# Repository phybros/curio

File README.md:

# CURIO

CURIO is an ESP8266 based dev board!

This repo is the KiCAD project for the board.

## Features

* USB-C
* ESP-12E/F WiFi module
* Compatible with Arduino
* Breadboard friendly
* Voltage divider for the `ADC0` pin

## More info

A more detailed writeup on the development of this board can be found at 
<https://willwarren.com/2023/05/09/curio-an-esp-12f-based-dev-board/>!

## License

This repo is licensed under Creative Commons Attribution-ShareAlike 4.0 
International.

Read the full license here: [LICENSE.txt](LICENSE.txt)

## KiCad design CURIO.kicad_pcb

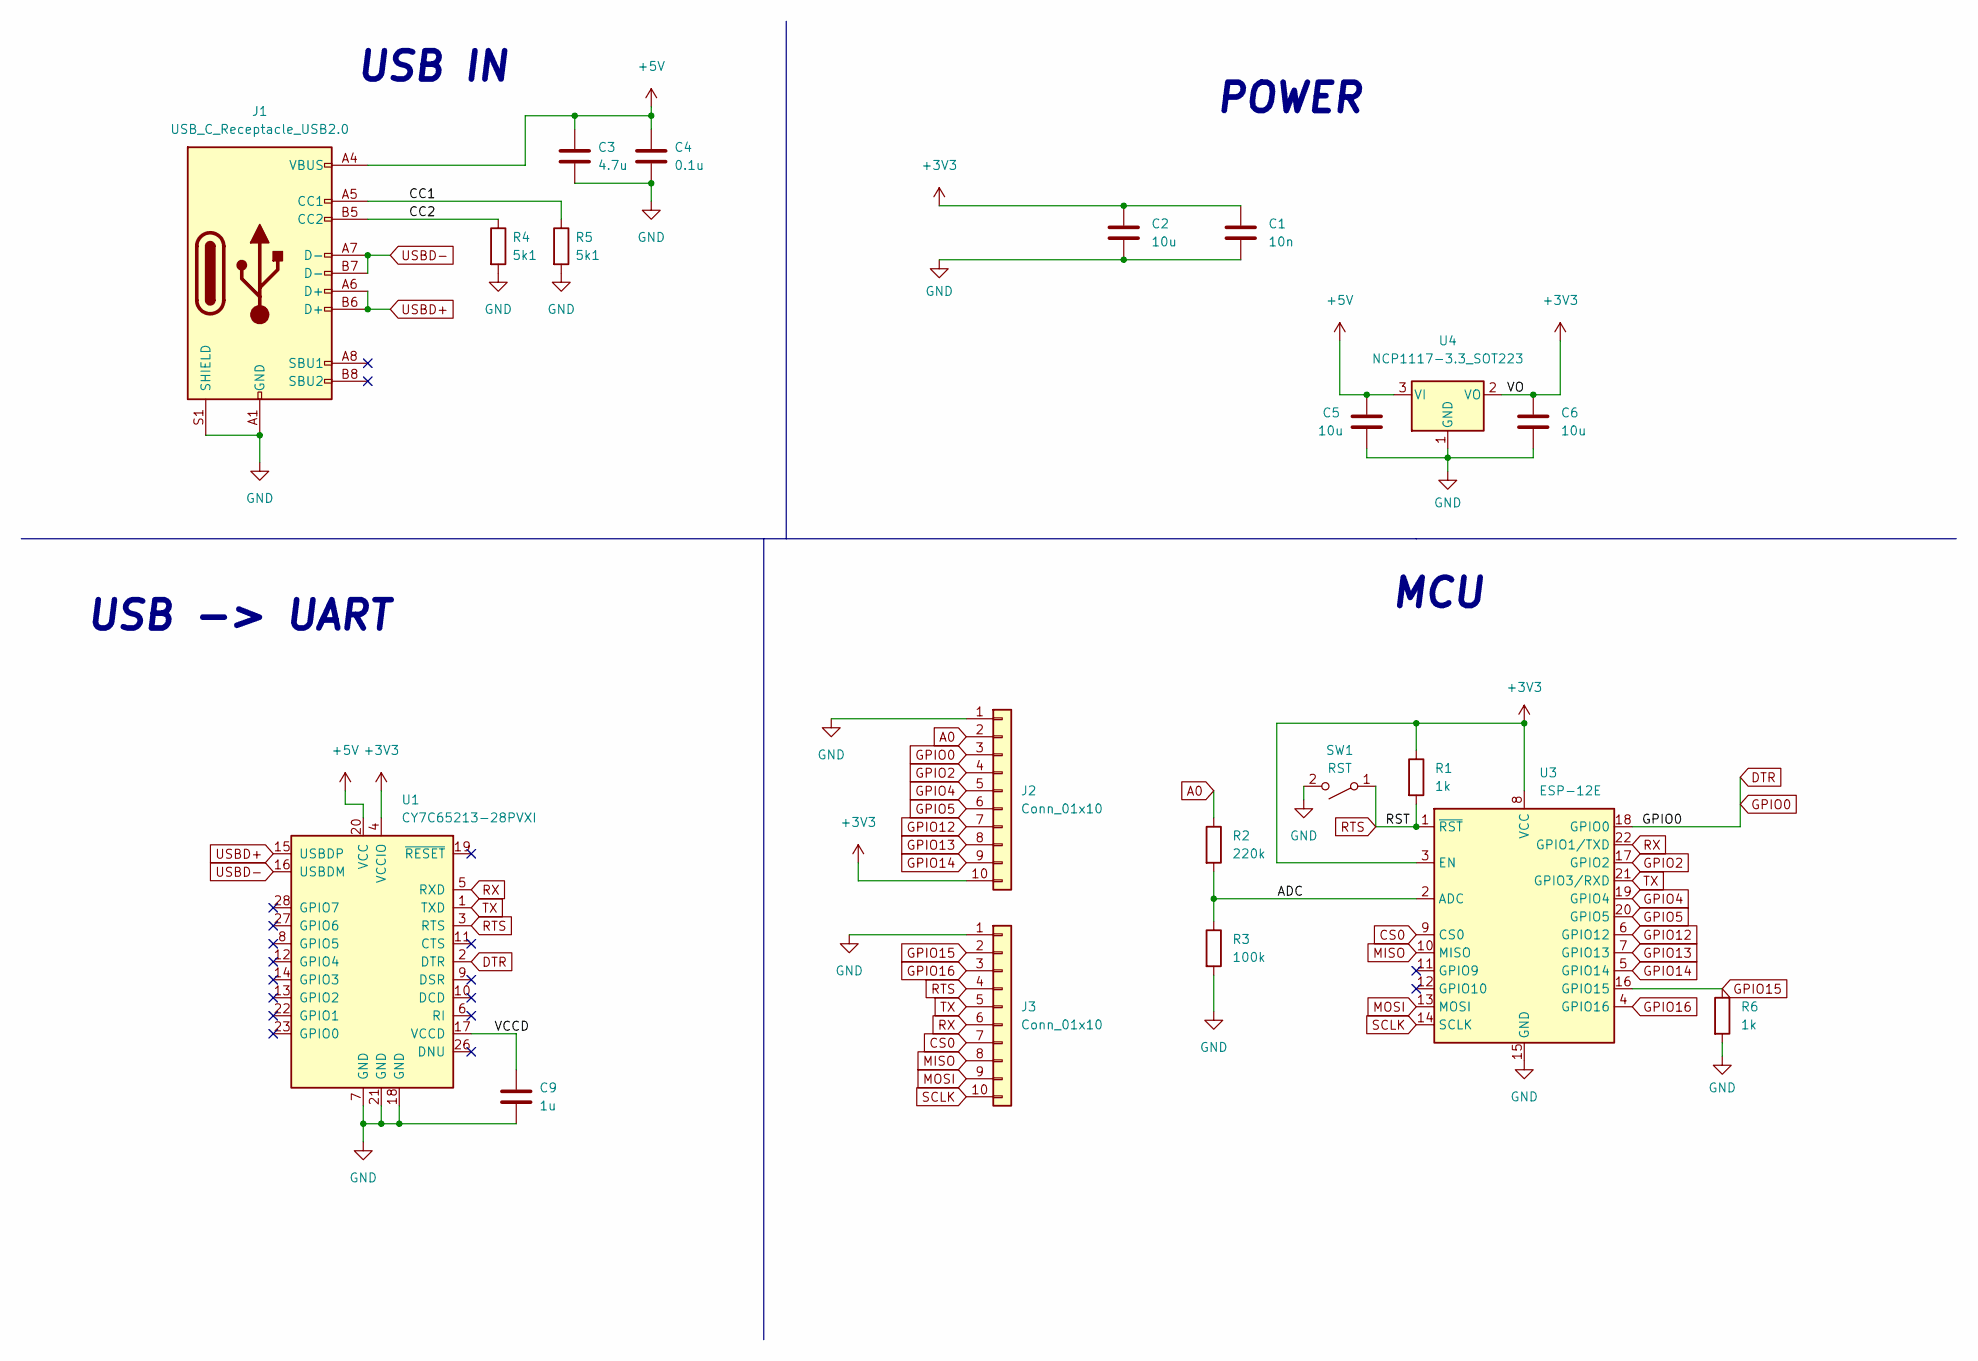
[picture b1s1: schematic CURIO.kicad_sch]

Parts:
C1: 10n; C_0402_1005Metric
C2, C5, C6: 10u; C_0402_1005Metric
C3: 4.7u; C_0402_1005Metric
C4: 0.1u; C_0402_1005Metric
C9: 1u; C_0402_1005Metric
J1: USB_C_Receptacle_USB2.0; USB_C_Receptacle_JAE_DX07S016JA1R1500
J2, J3: Conn_01x10; PinHeader_1x10_P2.54mm_Vertical
R1, R6: 1k; R_0402_1005Metric
R2: 220k; R_0402_1005Metric
R3: 100k; R_0402_1005Metric
R4, R5: 5k1; R_0402_1005Metric
SW1: RST; SW_SPST_B3U-1100P
U1: CY7C65213-28PVXI; SSOP-28_5.3x10.2mm_P0.65mm
U3: ESP-12E
U4: NCP1117-3.3_SOT223; SOT-223-3_TabPin2

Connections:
+3V3: C1.1, C2.1, C6.1, J2.10, R1.1, U1.4 (VCCIO), U3.3 (EN), U3.8 (VCC), U4.2 (VO)
+5V: C3.1, C4.1, C5.1, J1.A4 (VBUS), J1.A9 (VBUS), J1.B4 (VBUS), J1.B9 (VBUS), U1.20 (VCC), U4.3 (VI)
/ADC: R2.2, R3.1, U3.2 (ADC)
/CC1: J1.A5 (CC1), R5.1
/CC2: J1.B5 (CC2), R4.1
/VCCD: C9.1, U1.17 (VCCD)
A0: J2.2, R2.1
CS0: J3.7, U3.9 (CS0)
DTR: J2.3, U1.2 (DTR), U3.18 (GPIO0)
GND: C1.2, C2.2, C3.2, C4.2, C5.2, C6.2, C9.2, J1.A1 (GND), J1.A12 (GND), J1.B1 (GND), J1.B12 (GND), J1.S1 (SHIELD), J2.1, J3.1, R3.2, R4.2, R5.2, R6.2, SW1.2 (B), U1.7 (GND), U1.18 (GND), U1.21 (GND), U3.15 (GND), U4.1 (GND)
GPIO2: J2.4, U3.17 (GPIO2)
GPIO4: J2.5, U3.19 (GPIO4)
GPIO5: J2.6, U3.20 (GPIO5)
GPIO12: J2.7, U3.6 (GPIO12)
GPIO13: J2.8, U3.7 (GPIO13)
GPIO14: J2.9, U3.5 (GPIO14)
GPIO15: J3.2, R6.1, U3.16 (GPIO15)
GPIO16: J3.3, U3.4 (GPIO16)
MISO: J3.8, U3.10 (MISO)
MOSI: J3.9, U3.13 (MOSI)
RTS: J3.4, R1.2, SW1.1 (A), U1.3 (RTS), U3.1 (~RST)
RX: J3.6, U1.5 (RXD), U3.22 (GPIO1/TXD)
SCLK: J3.10, U3.14 (SCLK)
TX: J3.5, U1.1 (TXD), U3.21 (GPIO3/RXD)
USBD+: J1.A6 (D+), J1.B6 (D+), U1.15 (USBDP)
USBD-: J1.A7 (D-), J1.B7 (D-), U1.16 (USBDM)

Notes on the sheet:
USB IN
MCU
POWER
USB -> UART

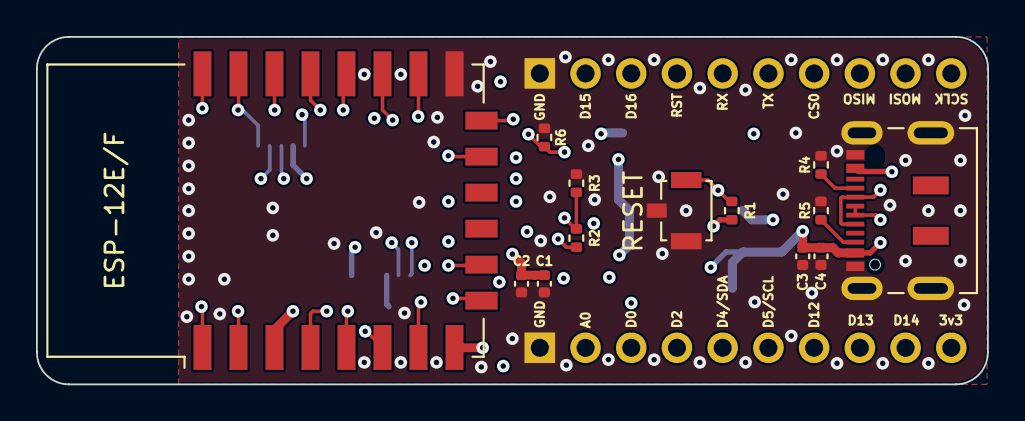
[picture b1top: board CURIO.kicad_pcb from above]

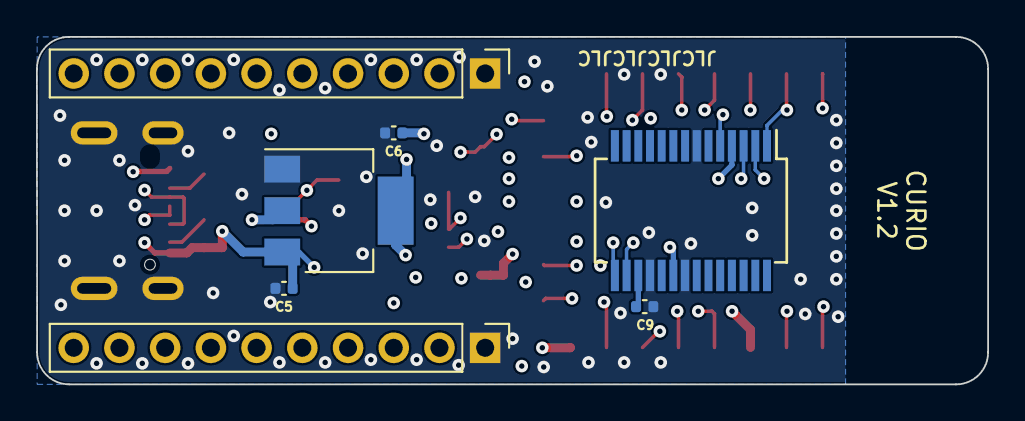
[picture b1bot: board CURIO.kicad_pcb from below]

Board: 4 copper layers, 52.8 x 19.3 mm, 20 parts (7 on the bottom side), 26 nets.

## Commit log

2023-05-09 add readme
